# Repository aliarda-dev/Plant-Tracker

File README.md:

***Plant Tracker***

DHT22 ve FC28 sensörlerini entegre çalıştırarak kodumda yazdığım koşullar sağlandığında telegram botuna mesaj yollayan bir IoT projesi. İlk IoT proje deneyimim oldu zorlandığım taraf ESP32'nin wifiye bağlaması oldu, buna gerçekten çok vakit ayırdım.

***Uğraştığım Hatalar***

* C make list mantığını biraz geç öğrendim bu yüzden compiler sürekli hata veriyordu
* Https sertifika hataları
* Main task overflow hatası, menucfonig defaultu 3584 bytedi ben bunu 8192 yaptim (https istekleri buna neden oldu)
* DHT22 Phase B hatası aldım. Çözümü delay kullanmak oldu wifi istekleri ile aynı anda kullanılınca sıkıntı çıkarabiliyor.
* RGB led 5V bağlı iken yanmıyordu. Sebebi ESP32'nin 5V çıkışının aktif olmamasıydı. Redditte dolaşmaktan projeden bıkmaya başlamıştım sonrasında kart üstündeki N-OUT köprüsünü öğrendim 5V güç çıkışı için bunun lehimlenmesi gerekiyormuş onu lehimledim.
* ve daha niceleri

***Donanım***

* ESP32S3
* DHT22 (Sıcaklık ve Nem sensörü)
* FC-28 (Toprak Nem Sensörü)
* Ortak Anot RGB Led
* 4x330R Direnç (Üç tanesi rgb led için geriye kalan bir tanesi de dht sensoru için)

***Nasıl Çalışır?***

* DHT22 sensöründen sıcaklık ve nem değerleri okunur ve gerekli variablelara aktarılır
* FC28 sensöründen nem değeri okunarak gerekli variablea aktarılır
* Wifi bağlantısı kurulur
* Belirlenen aralıkta telegram botuna bitkinin içinde bulunduğu odanın sıcaklık ve nem değerleri gönderilir
* Toprak nem değeri eşik değeri altına düşerse bota uyarı mesajı yollanır
* Sıcaklık ve nem değerleri belirlenen değerler dışına saparsa bota başka bir uyarı mesajı yollanır
* Zamanlama kontrolu olarak esp_timer_get_time() kullanılır

***Teknik Notlar***

* Wifi bağlantısı ve Telegram API kısmında AI'dan destek aldım. İlk IoT projem olduğu için ESP'nin ağ yapısını tek başıma kurmakta zorlandım. Kodu tamamladıktan sonra birkaç gün boyunca kullandığım her fonksiyonu ve event yapısını tek tek inceleyerek nasıl çalıştığını öğrenmeye çalıştım.

***Geliştirme Fikirleri***

* ESP32 hafızası üzerinde dosya açılarak hataların geldiği saatler data olarak tutulabilir.

🎥 Proje Demo

https://github.com/user-attachments/assets/45af9969-96e5-4f03-8e86-a813d68cf8f5

📷 Proje PCB Medyası

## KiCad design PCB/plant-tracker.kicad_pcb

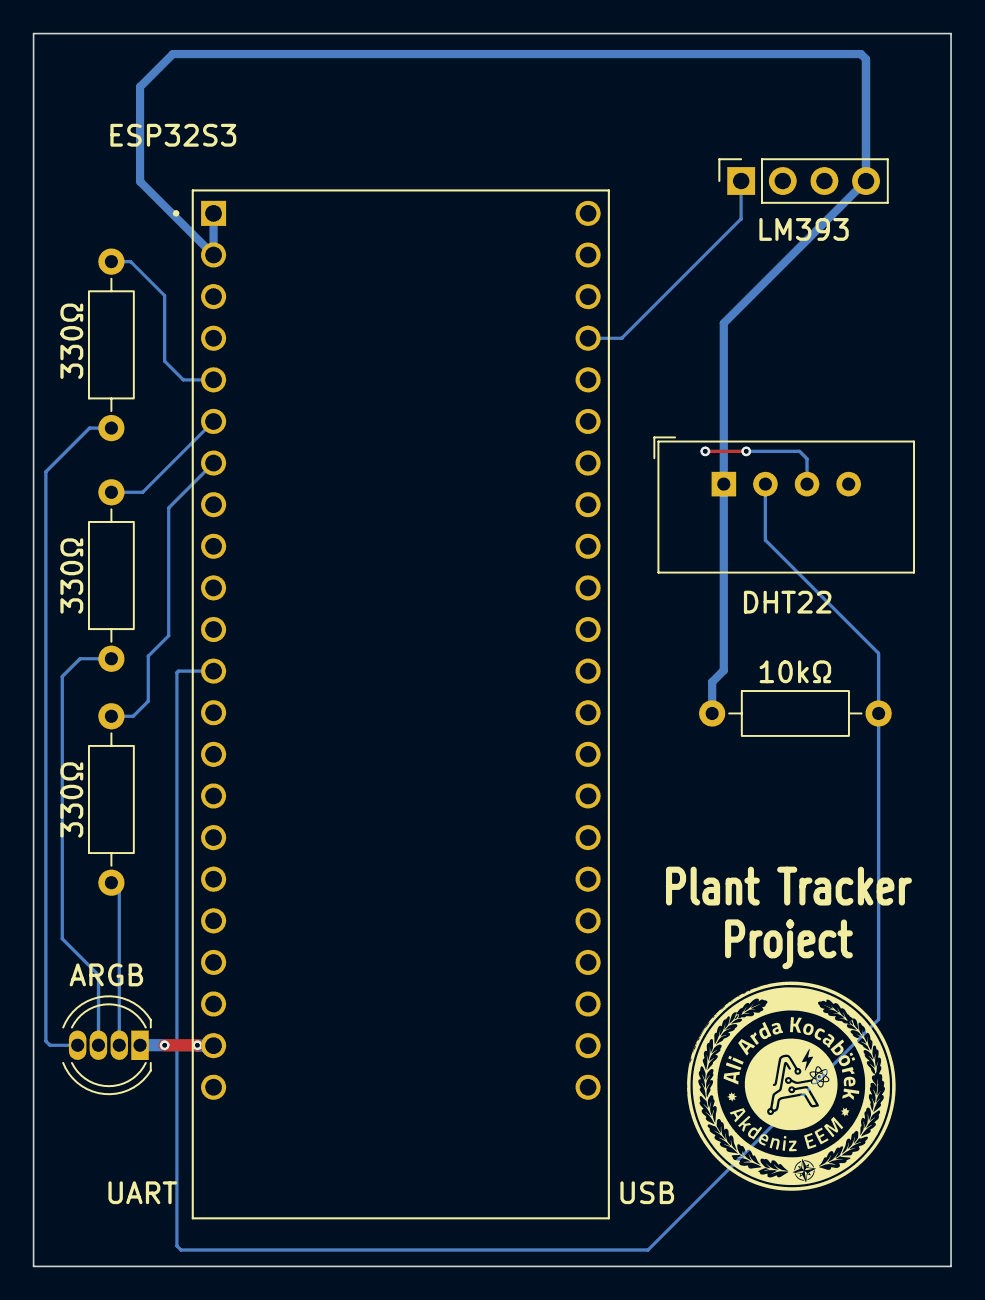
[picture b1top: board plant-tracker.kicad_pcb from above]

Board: 2 copper layers, 56.0 x 75.2 mm, 8 parts (0 on the bottom side), 11 nets.

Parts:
10kΩ: 10kR; R_Axial_DIN0207_L6.3mm_D2.5mm_P10.16mm_Horizontal
330Ω, 330Ω#2, 330Ω#3: 330R; R_Axial_DIN0207_L6.3mm_D2.5mm_P10.16mm_Horizontal
ARGB: LED_ARGB; LED_D5.0mm-4_RGB
DHT22: AM2302; ASAIR_AM2302_P2.54mm_Vertical
ESP32S3: ESP32-S3-DEVKITC-1-N8R2; ESP32S3
LM393: PinSocket_1x04_P2.54mm_Vertical

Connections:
3.3V: 10kΩ.1, DHT22.1 (VDD), ESP32S3.J1_1 (3V3), ESP32S3.J1_2 (3V3), LM393.4 (VCC)
5V: ARGB.1 (A), ESP32S3.J1_21 (5V0)
G1: ESP32S3.J3_4 (GPIO1), LM393.1 (AO)
G5: 330Ω#2.2, ESP32S3.J1_5 (GPIO5)
G6: 330Ω#3.2, ESP32S3.J1_6 (GPIO6)
G7: 330Ω.2, ESP32S3.J1_7 (GPIO7)
G8: 10kΩ.2, DHT22.2 (SDA), ESP32S3.J1_12 (GPIO8)
GND: DHT22.3 (GND), DHT22.4 (GND), ESP32S3.J1_22 (GND), ESP32S3.J3_1 (GND), ESP32S3.J3_21 (GND), ESP32S3.J3_22 (GND), LM393.3 (GND)
unnamed: 330Ω#2.1, ARGB.4 (BK)
unnamed: 330Ω#3.1, ARGB.3 (GK)
unnamed: 330Ω.1, ARGB.2 (RK)
